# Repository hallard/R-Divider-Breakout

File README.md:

Voltage divider breakout for 4 Channels ADS1015/ADS1115 ADC Board
=================================================================

This shield is used to decrease voltage input when it's higher than the embeded device can hold. For example with 3.3V devices we can't hold input W 3.3V and measuring for example Lipo Battery or Solar Panel voltage is not possible.
This board indroduce 
- 4 voltage divider 
- I2C ADS1x15 board compatible for devices that do not have enought ADC such as [WeMos][1]
- Footprint for 0805 caps for filtering input.

This board can fit on Adafruit [ADS1115][5] or [ADS1015][6] 

**In this case take care to just connect A0..A3 and GND to Adafruit board when stacking** other Adafruit board pins are used for input on my breakout.

**Waiting Boards from PCBs.io and OSHPark, I did not fully tested them yet, I will update ASAP. Use at your own risks**

Detailed Description
====================

Look at the schematics for more informations.

### Schematic

### Boards 

### Received boards

You can order the PCB of this board at [OSHPARK][4] or at [PCBs.io][3].
PCBs.io give me some reward when you order my designed boards from their site. This is pretty cool because I can use these rewards to create and design new boards and order boards for a discounted price, so if you don't care about PCB manufacturer please use PCBs.io.

### Assembled boards

Here is a picture of assembled board stacked with an ADS1115 ADC breakout

Take care when stacking, analog Input of breakout should not be connected to ADS1115 dedicated I2C and ADC control line, you'll need to use on long pin connector as follow

##License

You can do whatever you like with this design.

##Misc
See news and other projects on my [blog][1] 
 
[1]: http://www.wemos.cc/Products/d1_mini.html
[2]: https://hallard.me
[3]: https://PCBs.io/share/rJ1B8 
[4]: https://oshpark.com/shared_projects/vyab8UWr
[5]: https://www.adafruit.com/product/1085
[6]: https://www.adafruit.com/products/1083

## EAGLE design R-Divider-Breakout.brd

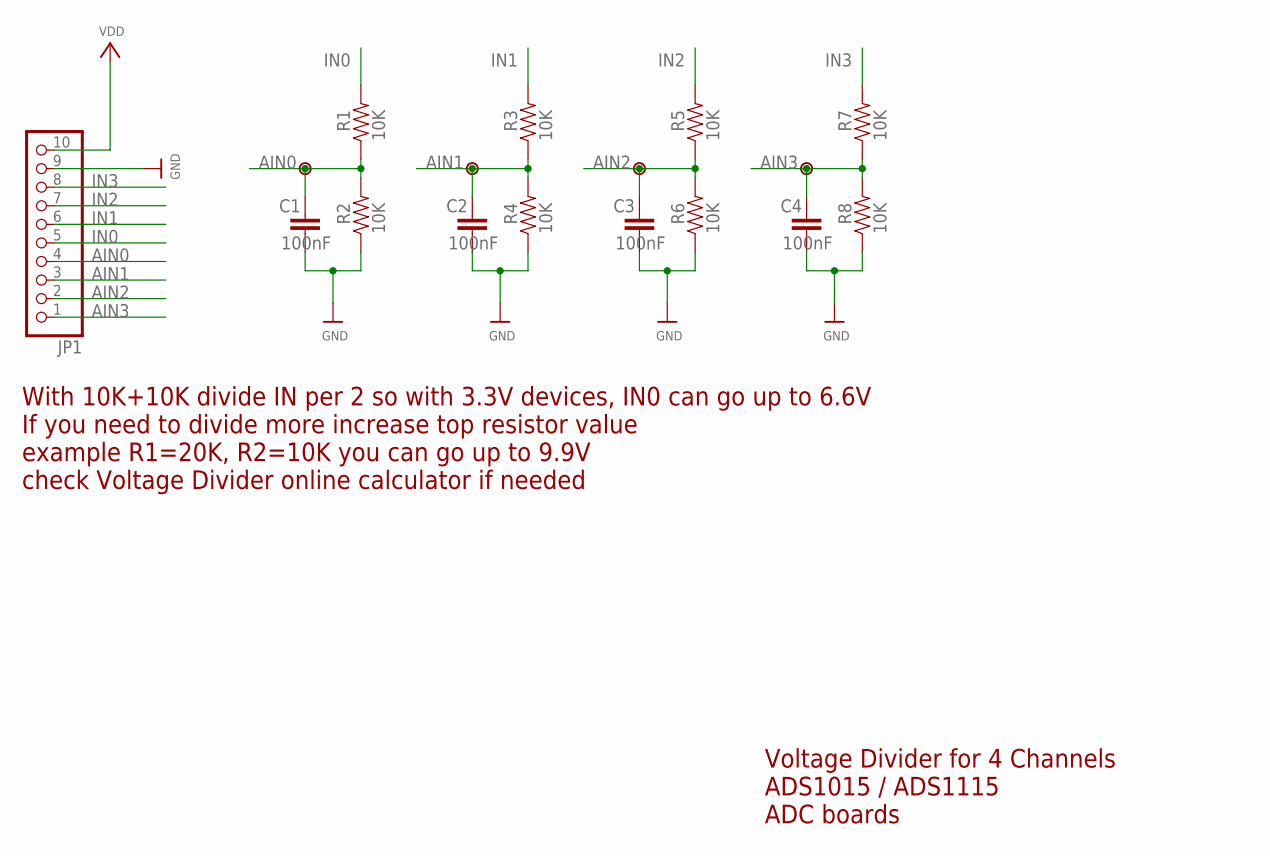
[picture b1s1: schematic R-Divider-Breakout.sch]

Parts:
C1, C2, C3, C4: 100nF; 0805-CAP
JP1: HEADER-1X1070MIL; 1X10_ROUND70
P1, P2, P3, P4: PADSMALL; PAD-SMALL
R1, R2, R3, R4, R5, R6, R7, R8: 10K; 0805-RES

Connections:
AIN0: C1.1, JP1.4, P1.1, R1.1, R2.2
AIN1: C2.1, JP1.3, P2.1, R3.1, R4.2
AIN2: C3.1, JP1.2, P3.1, R5.1, R6.2
AIN3: C4.1, JP1.1, P4.1, R7.1, R8.2
GND: C1.2, C2.2, C3.2, C4.2, JP1.9, R2.1, R4.1, R6.1, R8.1
IN0: JP1.5, R1.2
IN1: JP1.6, R3.2
IN2: JP1.7, R5.2
IN3: JP1.8, R7.2
VDD: JP1.10

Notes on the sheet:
Voltage Divider for 4 Channels ADS1015 / ADS1115 ADC boards
With 10K+10K divide IN per 2 so with 3.3V devices, IN0 can go up to 6.6V If you need to divide more increase top resistor value example R1=20K, R2=10K you can go up to 9.9V check Voltage Divider online calculator if needed

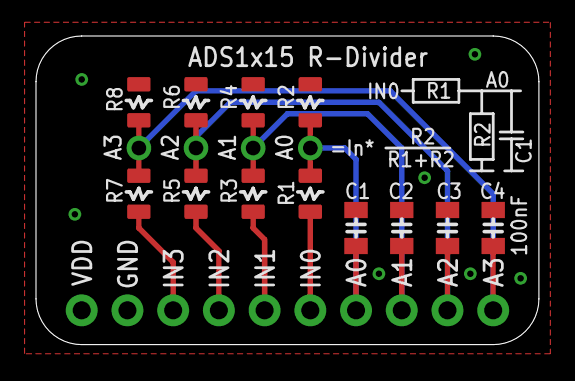
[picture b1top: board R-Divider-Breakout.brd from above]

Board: 2 copper layers, 27.9 x 17.1 mm, 18 parts (1 on the bottom side), 9 nets.

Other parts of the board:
U$5: LOGO_C2I_015

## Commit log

2016-08-02 :neckbeard: Added .gitattributes
2016-08-02 Creation
2016-08-02 Links errors
2016-08-02 Added info for stacking
2016-08-22 Received and mounted boards
2016-08-22 Link error

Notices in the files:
parts and their libraries:
SparkFun-Aesthetics: Licensing: Creative Commons ShareAlike 4.0 International - https://creativecommons.org/licenses/by-sa/4.0
